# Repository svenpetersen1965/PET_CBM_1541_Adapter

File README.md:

# PET_CBM_1541_Adapter
This is an adapter for connecting the 1541 (or other IEC floppy disk drives) to the Userport of a CBM8032 etc. It is the reconstruction of a hardware, that fits to an old EPROM, that was found in a CBM8032. Most likely, it works with other BASIC 4.0 CBM/PET computers.

For communication with the disk drive, a special instruction set is required.

•	each instruction starts with '!'<br> 
•	there are a couple of floppy disk related instructions, that have an alternative representation in the EPROM<br>
•	a !q will deactivate/quite the software<br>
•	a !@ will display the status of the 1541<br>
•	a !@"command" will send a command to the 1541<br>
•	No device number (,8) is required for any of the instructions<br>
•	The instructions are mostly standard BASIC4 instructions and can be short-cut as usually

!load"progname": 	       loads a program from 1541 <br>
!save"progname": 	       saves a program to 1541 <br>
!verify"progname":	       verifies a program <br>
!catalog: 	               displays the driectory of the floppy disk in the 1541 <br>
!open#SA,"file name": 	   it requires a # and after that it is a secondary address* <br>
!print#,"text": 	         prints a texts, also a secondary address after #* <br>
!get#: 	   * <br>
!close#SA: 	               closes a file, also a secondary address after #* <br>
!input#SA: *<br>  
!cmd: *<br>

The items marked with * require some further investigation. See the test documentation.

The software resides in a 2532 EPROM in UD11 and is started with SYS40960.

Find more in the project documentation and <a href="http://tech.guitarsite.de/cbm_1541_ada.html">my website</a> 

Mike Naberezny  did some further inverstigation of the EPROM binary/disassembly and has found out some interesting details. Check out his <a href="https://github.com/mnaberez/vc1541dos">github repository</a>.

# Fixes
The CB2 was improperly labled as CA2. This is fixed in the Gerbers v0a. This had no effect on the function of the circuit.

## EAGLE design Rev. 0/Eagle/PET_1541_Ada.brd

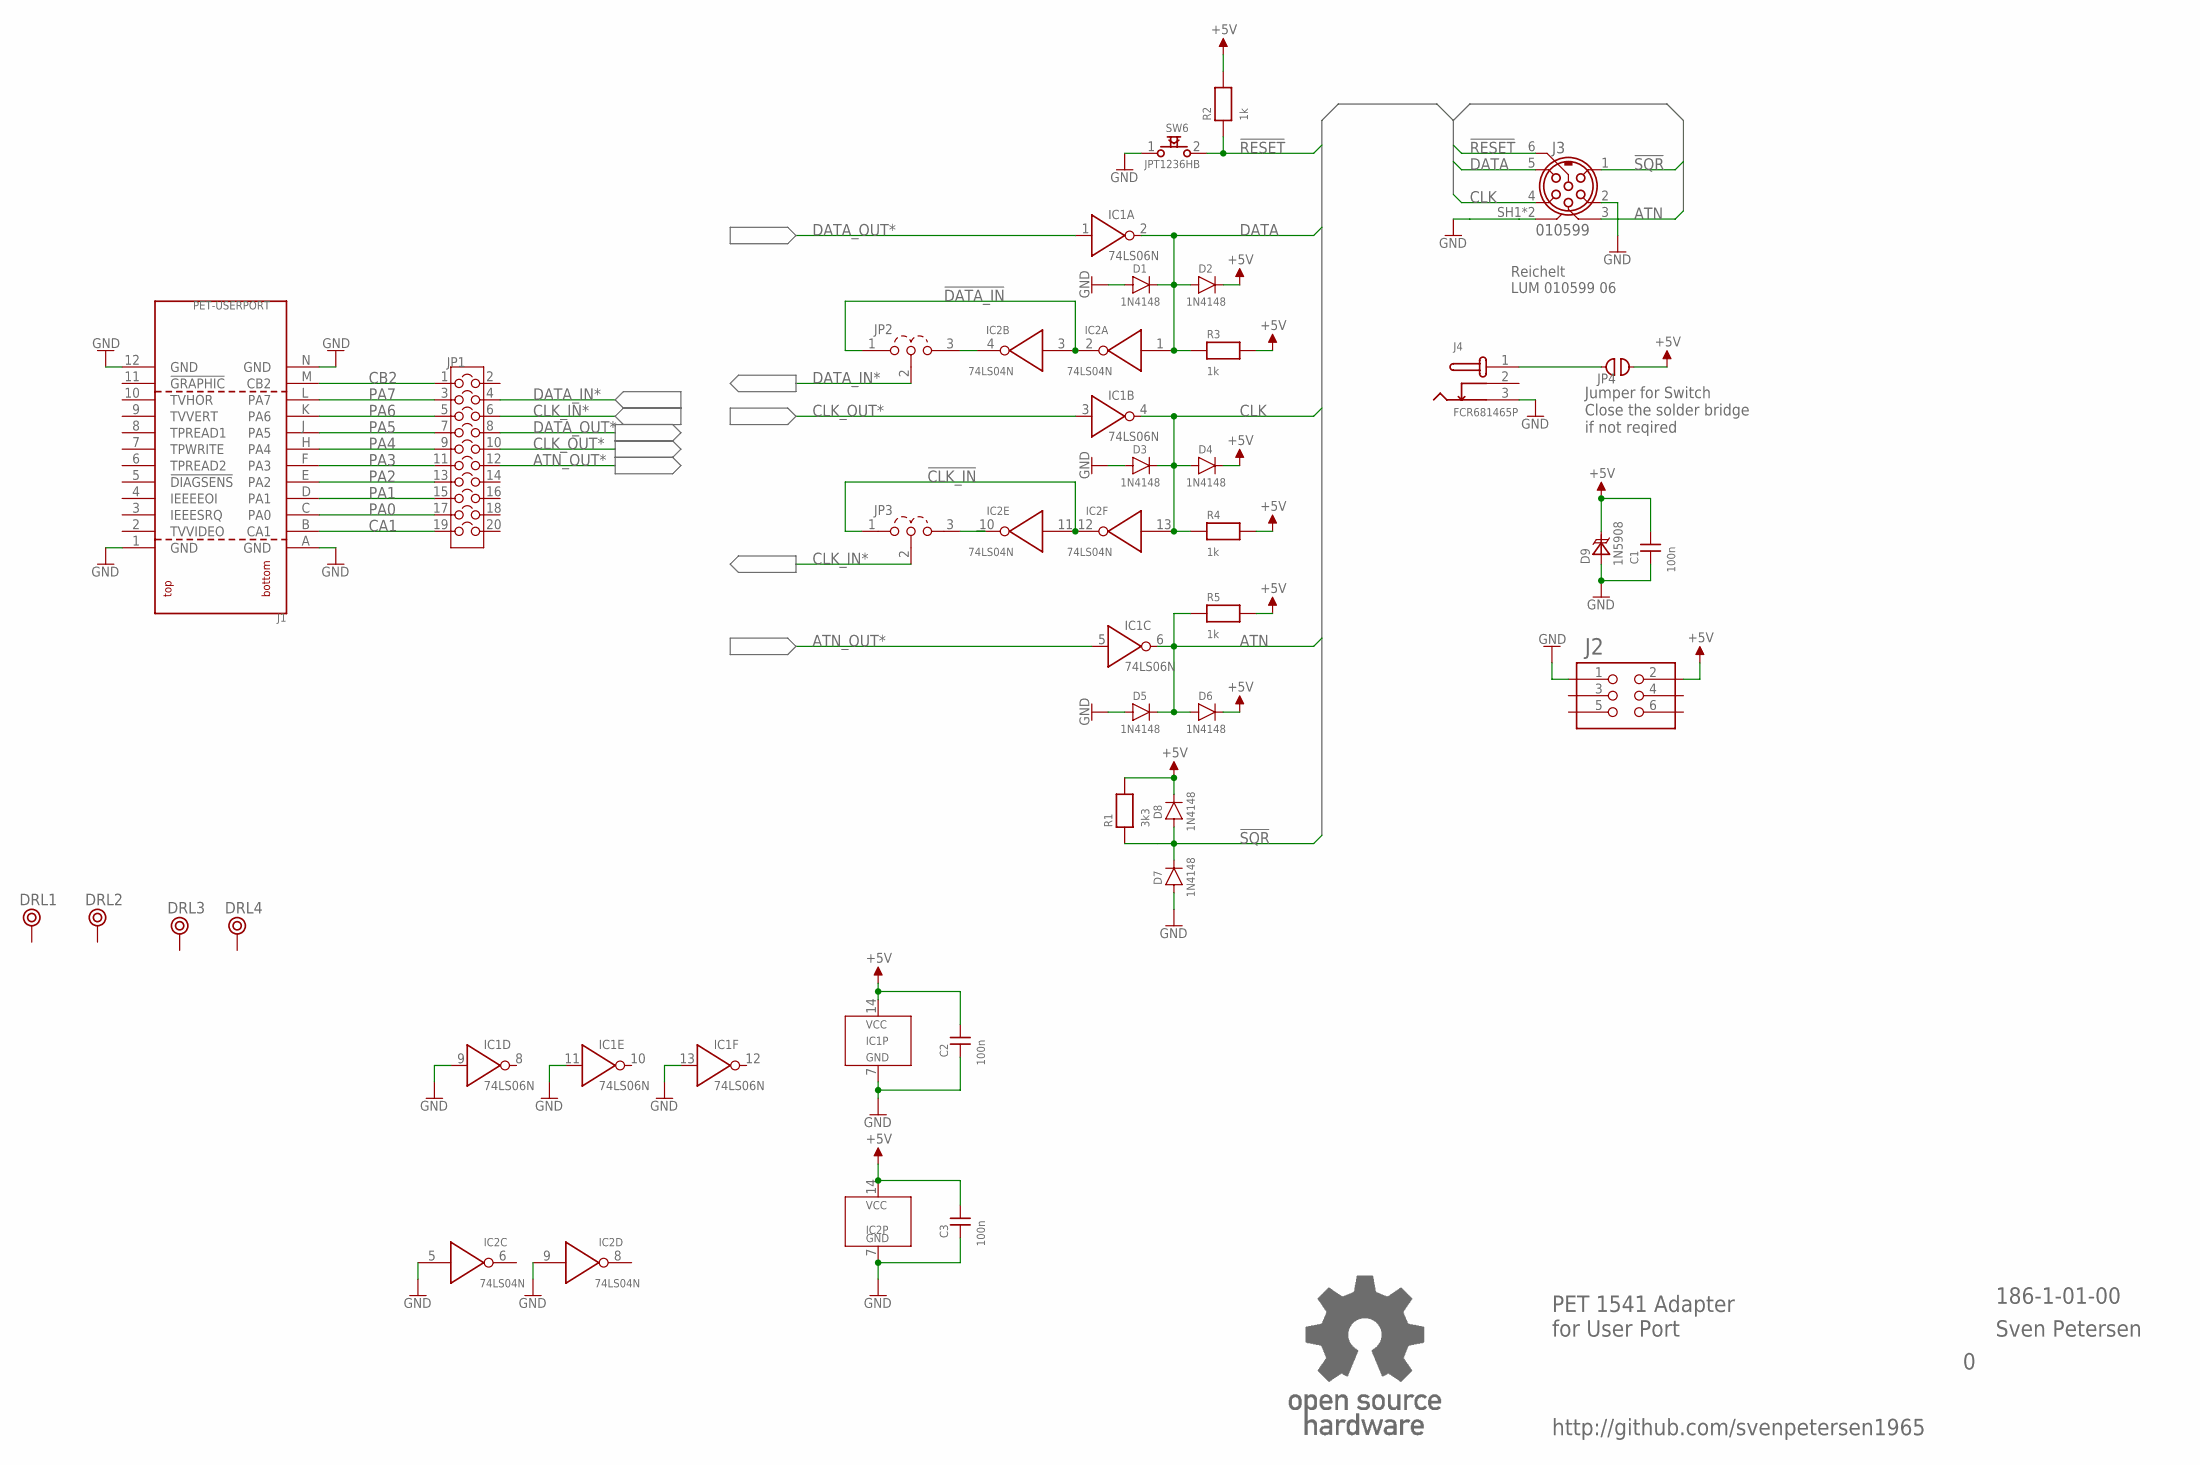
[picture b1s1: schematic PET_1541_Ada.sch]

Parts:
C1, C2, C3: 100n; C-2,5
D1, D2, D3, D4, D5, D6, D7, D8: 1N4148; DO-35/3
D9: 1N5908; CB429
DRL1, DRL2, DRL3, DRL4: BOHR3,5
IC1: 74LS06N; DIL-14
IC2: 74LS04N; DIL-14
J1: PET-USERPORT; USERPORT
J2: 2X03WV
J3: 010599
J4: FCR681465P
JP1: COMBI_2X10; COMBI-10X2
JP2, JP3: COMBI-3P
JP4: COMBI_2P; COMBI-2P
R1: 3k3; R-10
R2, R3, R4, R5: 1k; R-10
SW6: JPT1236HB; JTP_1236HB
U$2: OPEN_SOURCE_HW; OPENHW

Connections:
!CLK_IN: IC2.11 (I), IC2.12 (O), JP3.1
!DATA_IN: IC2.2 (O), IC2.3 (I), JP2.1
!RESET: J3.6, R2.1, SW6.2
!SQR: D7.K, D8.A, J3.1, R1.1
+5V: C1.2, C2.2, C3.2, D2.K, D4.K, D6.K, D8.K, D9.K, IC1.14 (VCC), IC2.14 (VCC), J2.2, JP4.2, R1.2, R2.2, R3.2, R4.2, R5.2
ATN: D5.K, D6.A, IC1.6 (O), J3.3, R5.1
ATN_OUT*: IC1.5 (I), JP1.12
CA1: J1.B (CA1), JP1.19
CB2: J1.M (CB2), JP1.1
CLK: D3.K, D4.A, IC1.4 (O), IC2.13 (I), J3.4, R4.1
CLK_IN: IC2.10 (O), JP3.3
CLK_IN*: JP1.6, JP3.2
CLK_OUT*: IC1.3 (I), JP1.10
DATA: D1.K, D2.A, IC1.2 (O), IC2.1 (I), J3.5, R3.1
DATA_IN: IC2.4 (O), JP2.3
DATA_IN*: JP1.4, JP2.2
DATA_OUT*: IC1.1 (I), JP1.8
GND: C1.1, C2.1, C3.1, D1.A, D3.A, D5.A, D7.A, D9.A, IC1.7 (GND), IC1.9 (I), IC1.11 (I), IC1.13 (I), IC2.5 (I), IC2.7 (GND), IC2.9 (I), J1.1 (GND), J1.12 (GND), J1.A (GND), J1.N (GND), J2.1, J3.2, J3.SH1 (SH), J3.SH2 (SH), J4.3, SW6.1
unnamed: J4.1, JP4.1
PA0: J1.C (PA0), JP1.17
PA1: J1.D (PA1), JP1.15
PA2: J1.E (PA2), JP1.13
PA3: J1.F (PA3), JP1.11
PA4: J1.H (PA4), JP1.9
PA5: J1.J (PA5), JP1.7
PA6: J1.K (PA6), JP1.5
PA7: J1.L (PA7), JP1.3

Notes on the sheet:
PET 1541 Adapter for User Port
186-1-01-00
Sven Petersen
http://github.com/svenpetersen1965
Reichelt LUM 010599 06
Jumper for Switch Close the solder bridge if not reqired

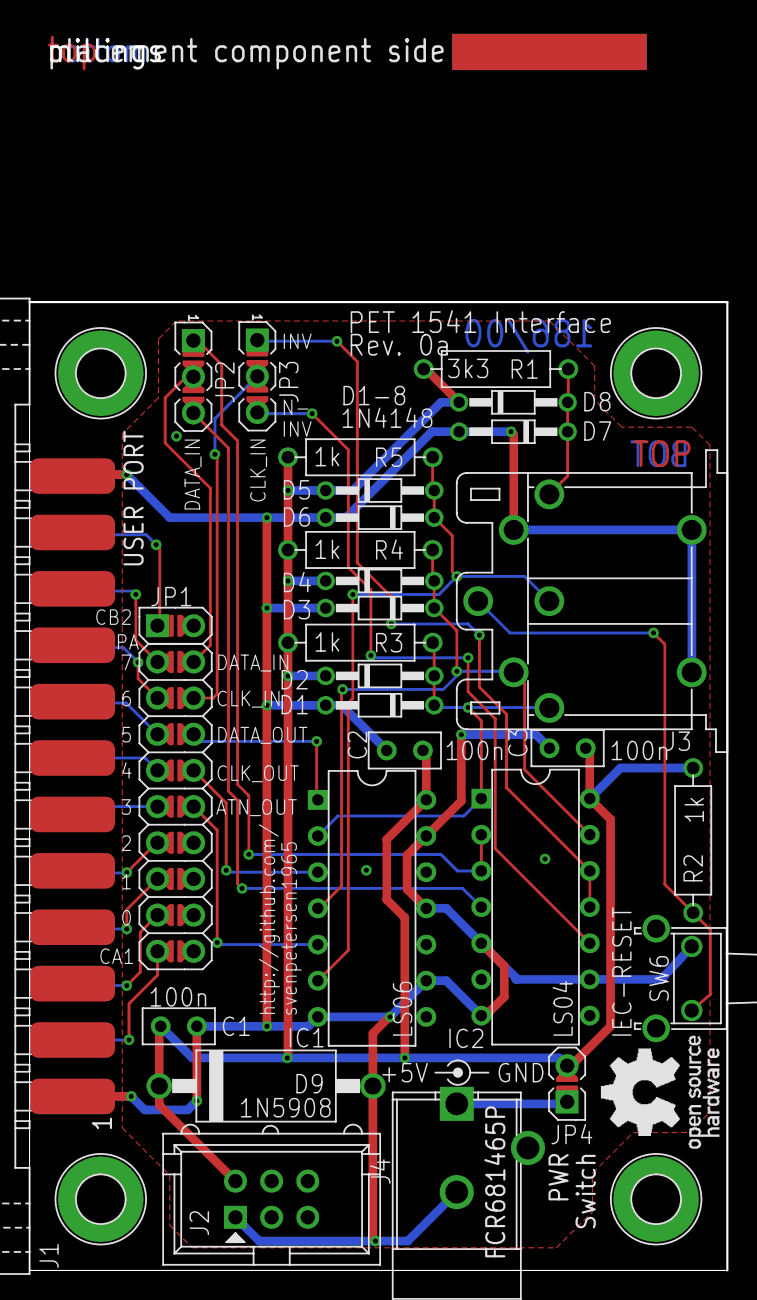
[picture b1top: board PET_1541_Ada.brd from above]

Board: 2 copper layers, 49.0 x 87.1 mm, 35 parts (0 on the bottom side), 27 nets.

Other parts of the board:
U$47: 2LAYER
U$48: PCB-TITLE/

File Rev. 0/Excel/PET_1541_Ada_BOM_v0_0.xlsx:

Commodore PET-1541-Adapter Rev. 0
Bill of Material Rev. 0.0
Pos. | Qty | Value | Footprint | Ref.-No. | Comment
1 | 1 | 186-2-01-00 | 2 Layer | PCB Rev. 0 | 2 layer, Cu 35µ, HASL, 68.0mm x 49.0mm, 1.6mm FR4
 | 1 | 2x3 box connector | 2X03WV | J2 | e.g. Reichelt WSL 6G
 | 1 | 10599 | 10599 | J3 | Lumberg, e.g. Reichelt 010599 06, tme.eu: 0105-06
 | 3 | 100n/50V | C-2,5 | C1, C2, C3 | ceramic capacitor, pitch: 2.5mm
 | 8 | 1N4148 |  | D1, D2, D3, D4, D5, D6, D7, D8 | standard silicon diode
 | 1 | 1N5908 | CB429 | D9 | TVS Diode (5V)
 | 4 | 1k | R-10 | R2, R3, R4, R5 | 1/4W, 1%
 | 1 | 3k3 | R-10 | R1 | 1/4W, 1%
 | 1 | 74LS04N | DIL-14 | IC2 | TI or other
 | 1 | 74LS06N | DIL-14 | IC1 | TI or other
 | 2 | COMBI-3P | COMBI-3P | JP2, JP3 | Solder bridge, see Module description
 | 1 | COMBI_2P | COMBI-2P | JP4 | Solder bridge, see Module description
 | 1 | COMBI_2X10 | COMBI-10X2 | JP1 | Solder bridge, see Module description
 | 1 | FCR681465P | FCR681465P | J4 | optional: Cliff, Reichelt: CLIFF FCR681465P, tme.eu: FCR681465P
 | 1 | JPT1236HB | JTP_1236HB | SW6 | TACT switch, 90°, Namae Electronics, e.g. Reichelt TASTER 3305B, tme.eu: TACTA-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
 | 1 | 2x12, 3.96mm pitch | USERPORT | J1 | edge connector, user port

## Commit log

2021-10-31 Initial release
2021-12-05 CB2 Silk screen fix
2021-12-05 CB2 silk screemn fix
2021-12-05 CB2 silk screen
2021-12-05 Gerber v0 is obsolete
2021-12-10 Remove unneeded jumper from build photo
2021-12-22 Picture with case
2021-12-22 3D printed case
2022-02-26 Gerbers removed
